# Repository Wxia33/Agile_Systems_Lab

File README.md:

# agile-systems-lab

**Agile Systems Lab** studies the neuromechanics of living systems.

This repository is for all code used in the Agile Systems Laboratory.

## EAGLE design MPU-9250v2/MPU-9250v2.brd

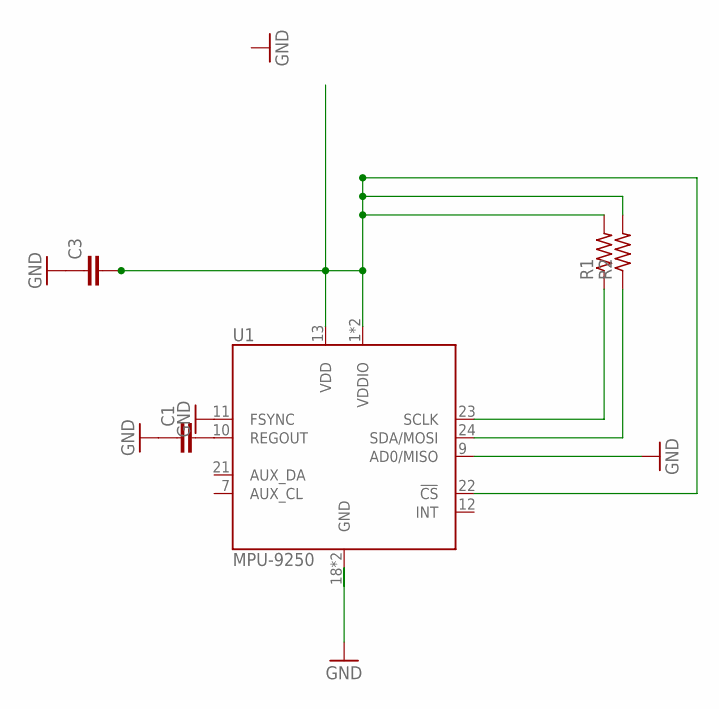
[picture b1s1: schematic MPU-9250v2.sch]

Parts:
C1, C3: CC0603; C0603
R1, R2: R-US_R0603; R0603
U1: MPU-9250; QFN-24/3MM

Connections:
GND: C1.1, C3.1, U1.9 (AD0/MISO), U1.11 (FSYNC), U1.18 (GND), U1.20 (GND)
unnamed: R2.1, U1.24 (SDA/MOSI)
unnamed: R1.1, U1.23 (SCLK)
unnamed: C3.2, R1.2, R2.2, U1.1 (VDDIO), U1.8 (VDDIO), U1.13 (VDD), U1.22 (!CS)
unnamed: C1.2, U1.10 (REGOUT)

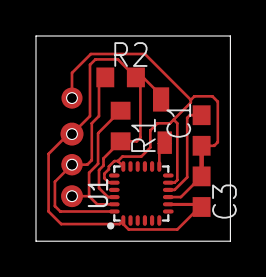
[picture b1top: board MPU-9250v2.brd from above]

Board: 2 copper layers, 10.8 x 11.4 mm, 5 parts (0 on the bottom side), 5 nets.

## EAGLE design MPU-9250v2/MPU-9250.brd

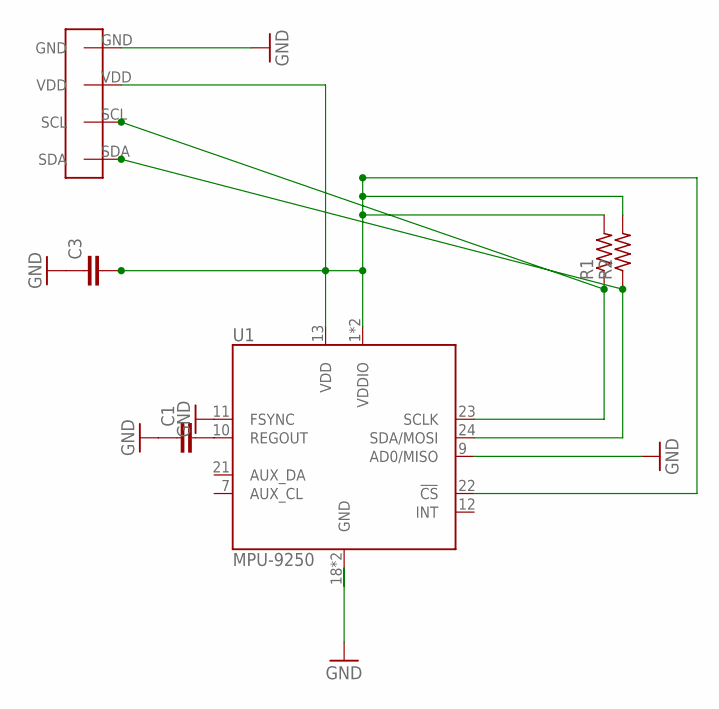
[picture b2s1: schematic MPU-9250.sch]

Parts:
C1, C3: CC0603; C0603
R1, R2: R-US_R0603; R0603
U1: MPU-9250; QFN-24/3MM
U$1: PINHEADER1MM

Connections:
GND: C1.1, C3.1, U1.9 (AD0/MISO), U1.11 (FSYNC), U1.18 (GND), U1.20 (GND), U$1.GND
unnamed: R2.1, U1.24 (SDA/MOSI), U$1.SDA
unnamed: R1.1, U1.23 (SCLK), U$1.SCL
unnamed: C3.2, R1.2, R2.2, U1.1 (VDDIO), U1.8 (VDDIO), U1.13 (VDD), U1.22 (!CS), U$1.VDD
unnamed: C1.2, U1.10 (REGOUT)

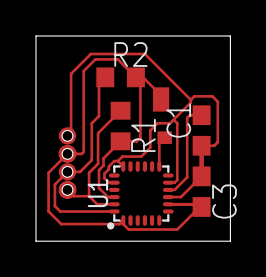
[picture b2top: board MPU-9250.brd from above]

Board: 2 copper layers, 10.8 x 11.4 mm, 6 parts (0 on the bottom side), 5 nets.

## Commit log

2016-08-05 Added Files
    Python code to record data from IMU Backpack
2016-08-05 Added Matlab Data Processing File
2016-08-11 Create MPU
2016-08-11 Create dfs
2016-08-11 Create FILE
2016-08-11 Move files
2016-08-11 Removed
2016-08-12 Added Eagle Files for PCB Manufacture
2016-08-12 Added Example Files for Robotis Controller
2016-08-12 Added PDF Files
2016-08-12 Added file to turn motors into wheels
